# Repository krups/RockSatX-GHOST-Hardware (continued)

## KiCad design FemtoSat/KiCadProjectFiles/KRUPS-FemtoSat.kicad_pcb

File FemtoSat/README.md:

# KRUPS-FemtoSat
PCB design files and documentation for the femto-satellites used in the University of Kentucky's 2025 RockSat-XG KRUPS payload

### PCB Render

### Components
- [Raspberry Pi Pico 2 W (4MB Flash)](https://datasheets.raspberrypi.com/picow/pico-2-w-datasheet.pdf)
- [Fanstel LR62XE 1W 868/915MHz LoRa Modem](https://static1.squarespace.com/static/561459a2e4b0b39f5cefa12e/t/63ddc4b1dd728b424f1a6c23/1675478197953/LR62E_LR62XE_M262X840XE_Product+Specifications.pdf)
- [BME280 Temperature, Pressure, Humidity Sensor](https://www.bosch-sensortec.com/media/boschsensortec/downloads/datasheets/bst-bme280-ds002.pdf)
- [BNO086 9-Axis IMU](https://www.mouser.com/datasheet/2/1480/BNO080_085_Datasheet-3196201.pdf)

### Pin Mapping
| Pico 2 W GPIO Pin | Net Name |
| --- | --- |
| GPIO6 | BNO086_HINTN |
| GPIO7 | BNO086_RESET (active low)|
| GPIO8 | I2C_SDA |
| GPIO9 | I2C_SCL |
| GPIO16 | SPI_MISO |
| GPIO17 | SPI_NSS |
| GPIO18 | SPI_CLK |
| GPIO19 | SPI_MOSI |
| GPIO20 | LORA_ANTSW |
| GPIO21 | LORA_RESET (active low)|
| GPIO22 | LORA_BUSY |
| GPIO26 | LORA_DIO1 |

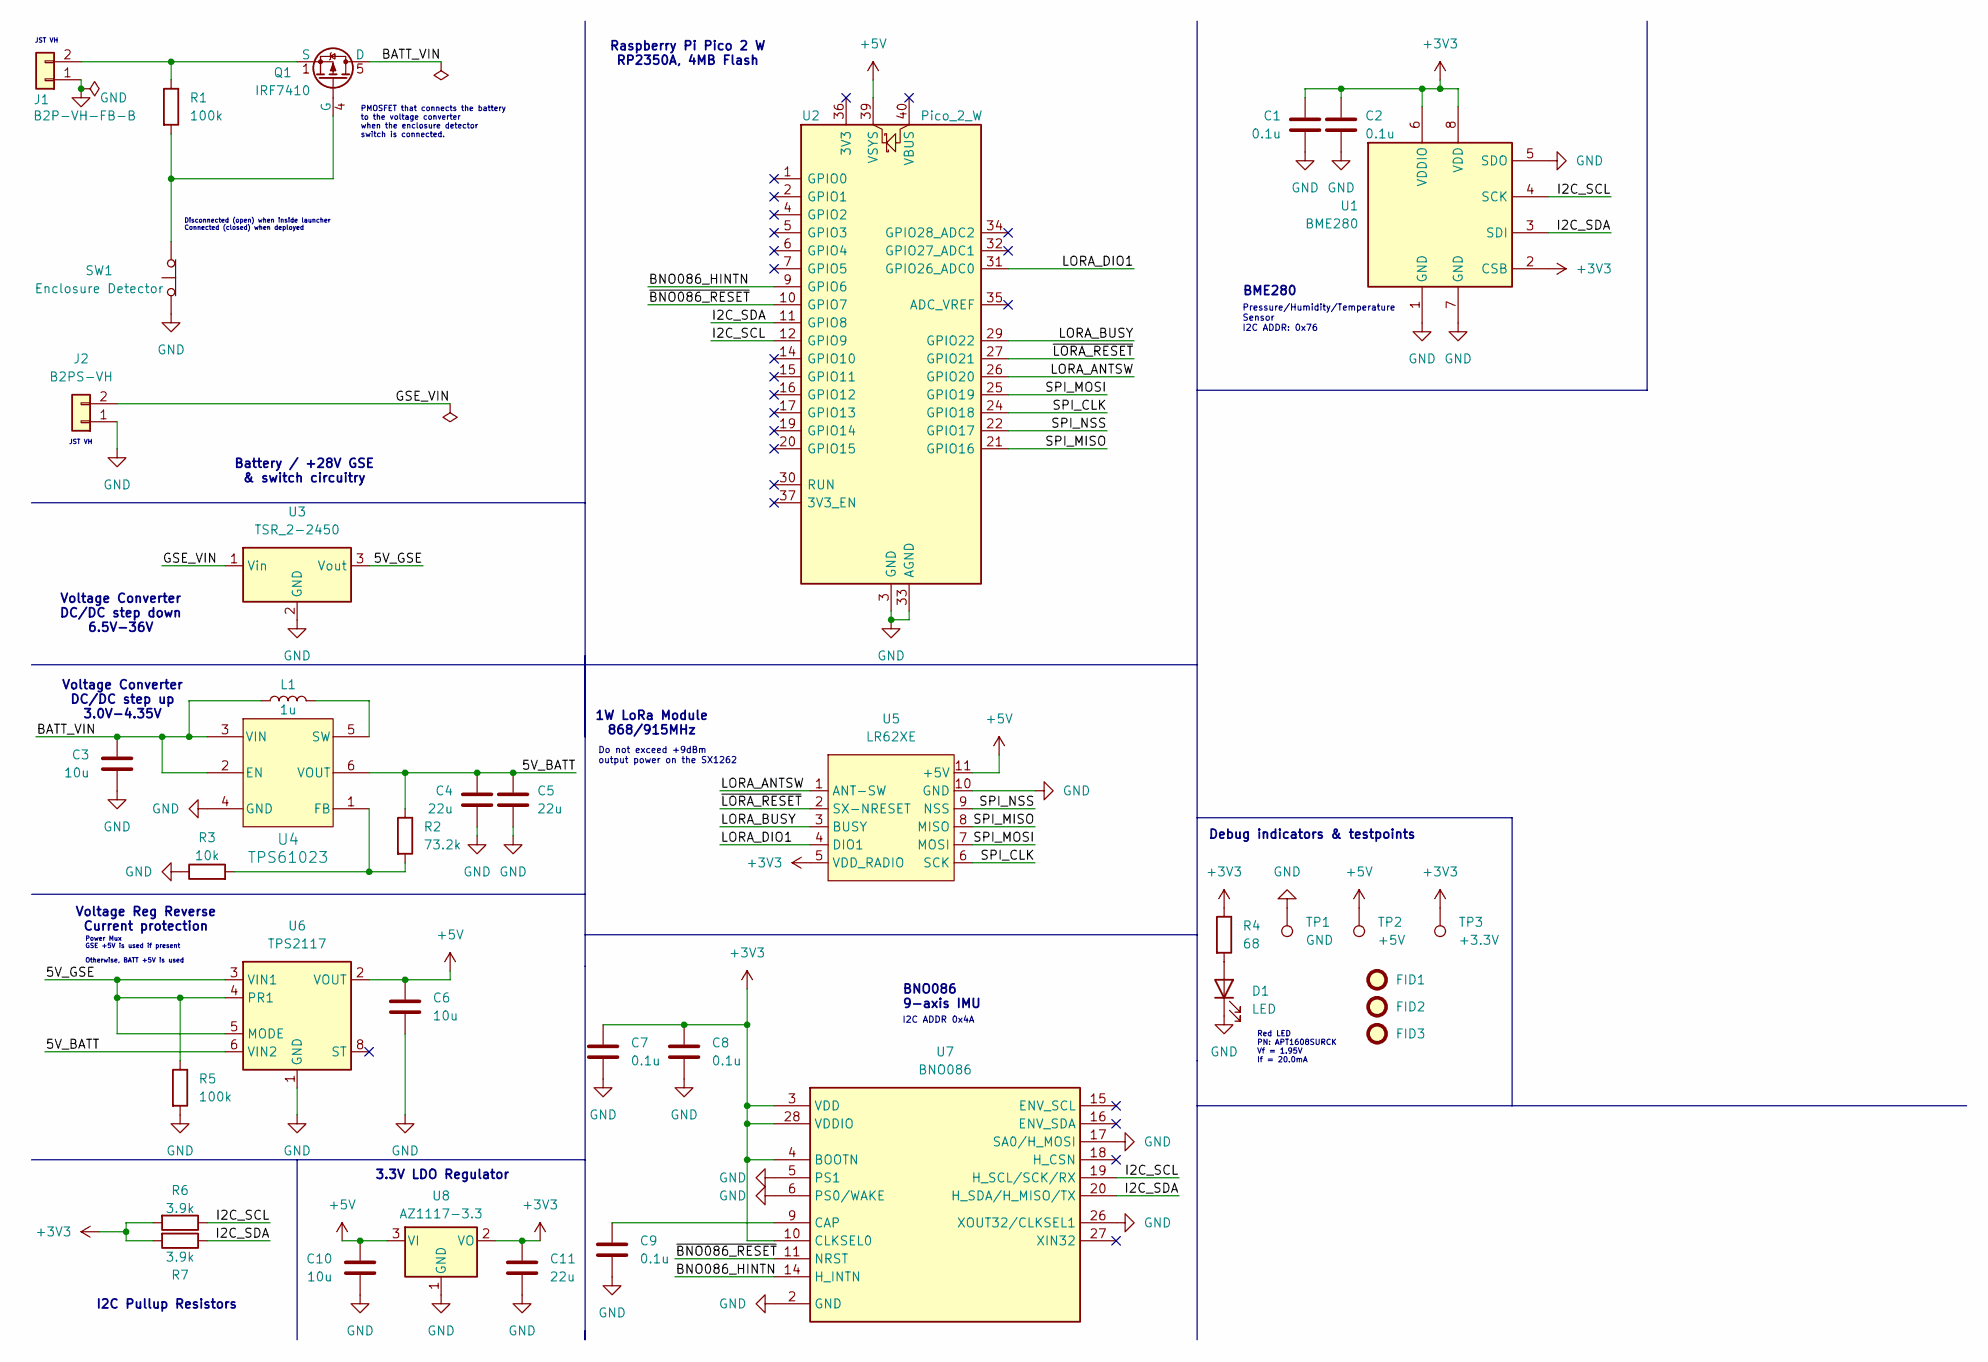
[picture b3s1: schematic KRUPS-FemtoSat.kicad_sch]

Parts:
C1, C2, C7, C8, C9: 0.1u; C_0603_1608Metric_Pad1.08x0.95mm_HandSolder; Digikey Part Number CC0603KRX7R7BB104
C3, C6, C10: 10u; C_0805_2012Metric_Pad1.18x1.45mm_HandSolder; Digikey Part Number CL21A106KOQNNNG
C4, C5, C11: 22u; C_0805_2012Metric_Pad1.18x1.45mm_HandSolder; Digikey Part Number CL21A226MPQNNNE
D1: LED; D_0603_1608Metric_Pad1.05x0.95mm_HandSolder; Digikey Part Number APT1608SURCK
FID1, FID2, FID3: Fiducial; Fiducial_0.5mm_Mask1mm
J1: B2P-VH-FB-B; JST_VH_B2P-VH-FB-B_1x02_P3.96mm_Vertical; Digikey Part Number B2P-VH-FB-B
J2: B2PS-VH; JST_VH_S2P-VH_1x02_P3.96mm_Horizontal; Digikey Part Number B2PS-VH
L1: 1u; L_Coilcraft_XxL4030; Digikey Part Number XEL4030-102MEC
Q1: IRF7410; SOIC-8_3.9x4.9mm_P1.27mm; Digikey Part Number IRF7410TRPBF
R1, R5: 100k; R_0603_1608Metric_Pad0.98x0.95mm_HandSolder; Digikey Part Number RMCF0603FT100K
R2: 73.2k; R_0603_1608Metric_Pad0.98x0.95mm_HandSolder; Digikey Part Number RC0603FR-0773K2L
R3: 10k; R_0603_1608Metric_Pad0.98x0.95mm_HandSolder; Digikey Part Number RC0603FR-0710KL
R4: 68; R_0603_1608Metric_Pad0.98x0.95mm_HandSolder; Digikey Part Number RC0603JR-0768RL
R6, R7: 3.9k; R_0603_1608Metric_Pad0.98x0.95mm_HandSolder; Digikey Part Number ERJ-3EKF3901V
SW1: Enclosure Detector; LC1258OANP; Digikey Part Number LC1258OANP
TP1: GND; TestPoint_Pad_2.0x2.0mm
TP2: +5V; TestPoint_Pad_2.0x2.0mm
TP3: +3.3V; TestPoint_Pad_2.0x2.0mm
U1: BME280; Bosch_LGA-8_2.5x2.5mm_P0.65mm_ClockwisePinNumbering; Digikey Part Number BME280
U2: Pico_2_W; RaspberryPi_Pico2_W_SMD; Digikey Part Number 2648-SC1633CT-ND
U3: TSR_2-2450; CONV_TSR_2-2450; Digikey Part Number TSR 2-2450
U4: TPS61023; SOT-563; Digikey Part Number TPS61023DRLR
U5: LR62XE; Digikey Part Number LR62XE
U6: TPS2117; SOT-583-8; Digikey Part Number TPS2117DRLR
U7: BNO086; LGA-28_5.2x3.8mm_P0.5mm; Manufacturer_Part_Number BNO086; Mouser Part Number 526-BNO086
U8: AZ1117-3.3; SOT-89-3_Handsoldering; Digikey Part Number AZ1117CR2-3.3TRG1

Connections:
+3V3: C1.1, C2.1, C7.1, C8.1, C11.1, R4.1, R6.2, R7.2, TP3.1, U1.2 (CSB), U1.6 (VDDIO), U1.8 (VDD), U5.5 (VDD_RADIO), U7.3 (VDD), U7.4 (BOOTN), U7.10 (CLKSEL0), U7.28 (VDDIO), U8.2 (VO)
+5V: C6.1, C10.1, TP2.1, U2.39 (VSYS), U5.11 (+5V), U6.2 (VOUT), U6.7 (VOUT), U8.3 (VI)
/5V_BATT: C4.1, C5.1, R2.1, U4.6 (VOUT), U6.6 (VIN2)
/5V_GSE: R5.1, U3.3 (Vout), U6.3 (VIN1), U6.4 (PR1), U6.5 (MODE)
/BATT_VIN: C3.1, L1.1, Q1.5 (D), Q1.6, Q1.7, Q1.8, U4.2 (EN), U4.3 (VIN)
/BNO086_HINTN: U2.9 (GPIO6), U7.14 (H_INTN)
/GSE_VIN: J2.2, U3.1 (Vin)
/I2C_SCL: R6.1, U1.4 (SCK), U2.12 (GPIO9), U7.19 (H_SCL/SCK/RX)
/I2C_SDA: R7.1, U1.3 (SDI), U2.11 (GPIO8), U7.20 (H_SDA/H_MISO/TX)
/LORA_ANTSW: U2.26 (GPIO20), U5.1 (ANT-SW)
/LORA_BUSY: U2.29 (GPIO22), U5.3 (BUSY)
/LORA_DIO1: U2.31 (GPIO26_ADC0), U5.4 (DIO1)
/SPI_CLK: U2.24 (GPIO18), U5.6 (SCK)
/SPI_MISO: U2.21 (GPIO16), U5.8 (MISO)
/SPI_MOSI: U2.25 (GPIO19), U5.7 (MOSI)
/SPI_NSS: U2.22 (GPIO17), U5.9 (NSS)
/~BNO086_RESET: U2.10 (GPIO7), U7.11 (NRST)
/~LORA_RESET: U2.27 (GPIO21), U5.2 (SX-NRESET)
GND: C1.2, C2.2, C3.2, C4.2, C5.2, C6.2, C7.2, C8.2, C9.2, C10.2, C11.2, D1.1 (K), J1.1, J2.1, R3.1, R5.2, SW1.1 (A), TP1.1, U1.1 (GND), U1.5 (SDO), U1.7 (GND), U2.3 (GND), U2.8 (GND), U2.13 (GND), U2.18 (GND), U2.23 (GND), U2.28 (GND), U2.33 (AGND), U2.38 (GND), U3.2 (GND), U4.4 (GND), U5.10 (GND), U5.12 (GND), U6.1 (GND), U7.2 (GND), U7.5 (PS1), U7.6 (PS0/WAKE), U7.17 (SA0/H_MOSI), U7.25 (GND), U7.26 (XOUT32/CLKSEL1), U8.1 (GND)
unnamed: D1.2 (A), R4.2
unnamed: J1.2, Q1.1 (S), Q1.2, Q1.3, R1.1
unnamed: Q1.4 (G), R1.2, SW1.2 (B)
unnamed: R2.2, R3.2, U4.1 (FB)
unnamed: L1.2, U4.5 (SW)
unnamed: C9.1, U7.9 (CAP)

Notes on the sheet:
Power Mux GSE +5V is used if present Otherwise, BATT +5V is used
I2C ADDR 0x4A
JST VH
Red LED PN: APT1608SURCK Vf = 1.95V If = 20.0mA
Pressure/Humidity/Temperature Sensor I2C ADDR: 0x76
3.3V LDO Regulator
I2C Pullup Resistors
Voltage Converter DC/DC step down 6.5V-36V
Disconnected (open) when inside launcher Connected (closed) when deployed
Battery / +28V GSE & switch circuitry
PMOSFET that connects the battery to the voltage converter when the enclosure detector switch is connected.
Voltage Reg Reverse Current protection
BNO086 9-axis IMU
BME280
Do not exceed +9dBm output power on the SX1262
Raspberry Pi Pico 2 W RP2350A, 4MB Flash
Debug indicators & testpoints
1W LoRa Module 868/915MHz
Voltage Converter DC/DC step up 3.0V-4.35V

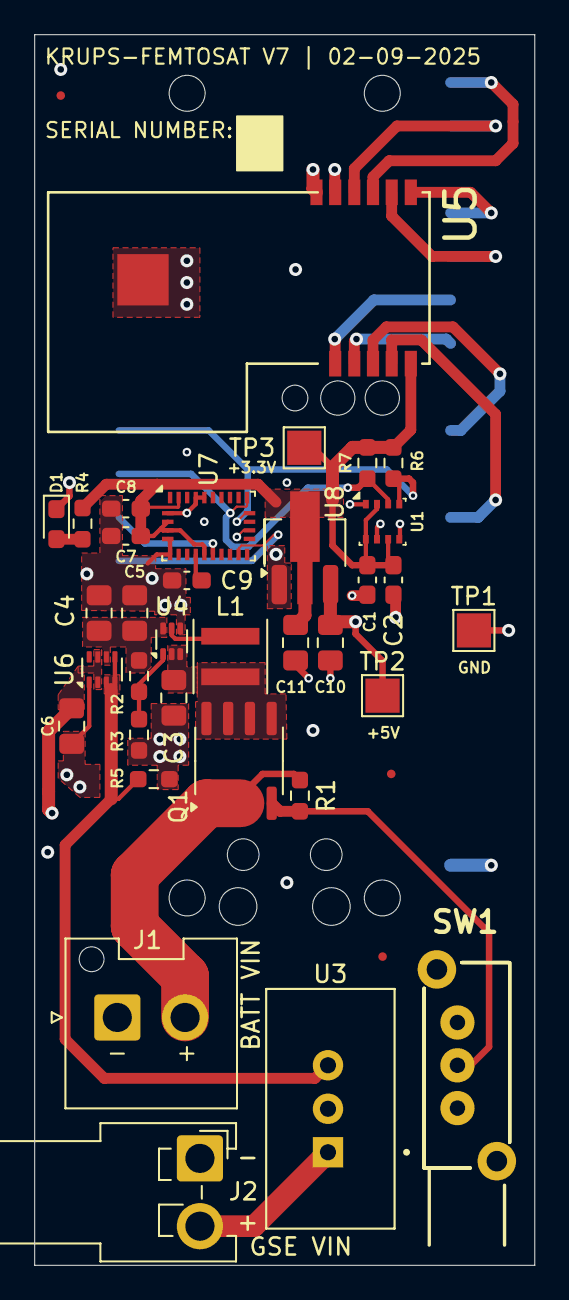
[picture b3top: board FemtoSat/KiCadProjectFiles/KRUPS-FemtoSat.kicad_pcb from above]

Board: 4 copper layers, 29.2 x 71.9 mm, 38 parts (1 on the bottom side), 25 nets.

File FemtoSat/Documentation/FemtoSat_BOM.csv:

"Reference","Value","Description","Qty","Digikey Part Number","DNP"
"C1,C2,C7,C8,C9","0.1u","0.1uF, 16V, X7R, SMD 0603","5","CC0603KRX7R7BB104",""
"C3,C6,C10","10u","10uF, 16V, X5R, SMD 0805","3","CL21A106KOQNNNG",""
"C4,C5,C11","22u","22uF, 10V, X5R, SMD 0805","3","CL21A226MPQNNNE",""
"D1","LED","LED, 1.95V Vf, 20mA If, SMD 0603","1","APT1608SURCK",""
"J1","B2P-VH-FB-B","JST-VH 2 Pin Connector, Shielded, Vertical","1","B2P-VH-FB-B",""
"J2","B2PS-VH","JST-VH 2 Pin Connector, Horizontal","1","B2PS-VH",""
"L1","1u","1uH Inductor, Shielded","1","XEL4030-102MEC",""
"Q1","IRF7410","PMOSFET, SOIC-8","1","IRF7410TRPBF",""
"R1,R5","100k","100K OHM, 1%, 1/10W, SMD 0603","2","RMCF0603FT100K",""
"R2","73.2k","73.2K OHM, 1%, 1/10W, SMD 0603","1","RC0603FR-0773K2L",""
"R3","10k","10K OHM, 1%, 1/10W, SMD 0603","1","RC0603FR-0710KL",""
"R4","68","68 OHM, 5%, 1/10W, SMD 0603","1","RC0603JR-0768RL",""
"R6,R7","3.9k","3.9K OHM, 1%, 1/10W, SMD 0603","2","ERJ-3EKF3901V",""
"SW1","Enclosure Detector","SPDT Push Switch, Non-Latching","1","LC1258OANP",""
"U1","BME280","3-in-1 sensor, humidity, pressure, temperature, I2C and SPI interface, 1.71-3.6V, LGA-8","1","BME280",""
"U2","Pico_2_W","Versatile and inexpensive microcontroller module powered by an RP2350 dual-core processor","1","2648-SC1633CT-ND",""
"U3","TSR_2-2450","1A step-down regulator module, fixed 5V output voltage, 5-36V input voltage, -40°C to +85°C temperature range, TO-220 compatible LM78xx replacement","1","TSR 2-2450",""
"U4","TPS61023","TPS61023 Boost Converter","1","TPS61023DRLR",""
"U5","LR62XE","1W LoRa Module","1","LR62XE",""
"U6","TPS2117","2 Channnels Power Mux with Manual and Priority Switchover, 1.6-5.5V Input Voltage, 2.5A Output Current, Ron 40 mOhm, SOT-583-8","1","TPS2117DRLR",""
"U7","BNO086","Accelerometer, Gyroscope, Magnetometer, Temperature, 9 Axis Sensor IC, SPI Output","1","BNO086",""
"U8","AZ1117-3.3","1A 20V Fixed LDO Linear Regulator, 3.3V, SOT-89/SOT-223/TO-220/TO-252/TO-263","1","AZ1117CR2-3.3TRG1",""

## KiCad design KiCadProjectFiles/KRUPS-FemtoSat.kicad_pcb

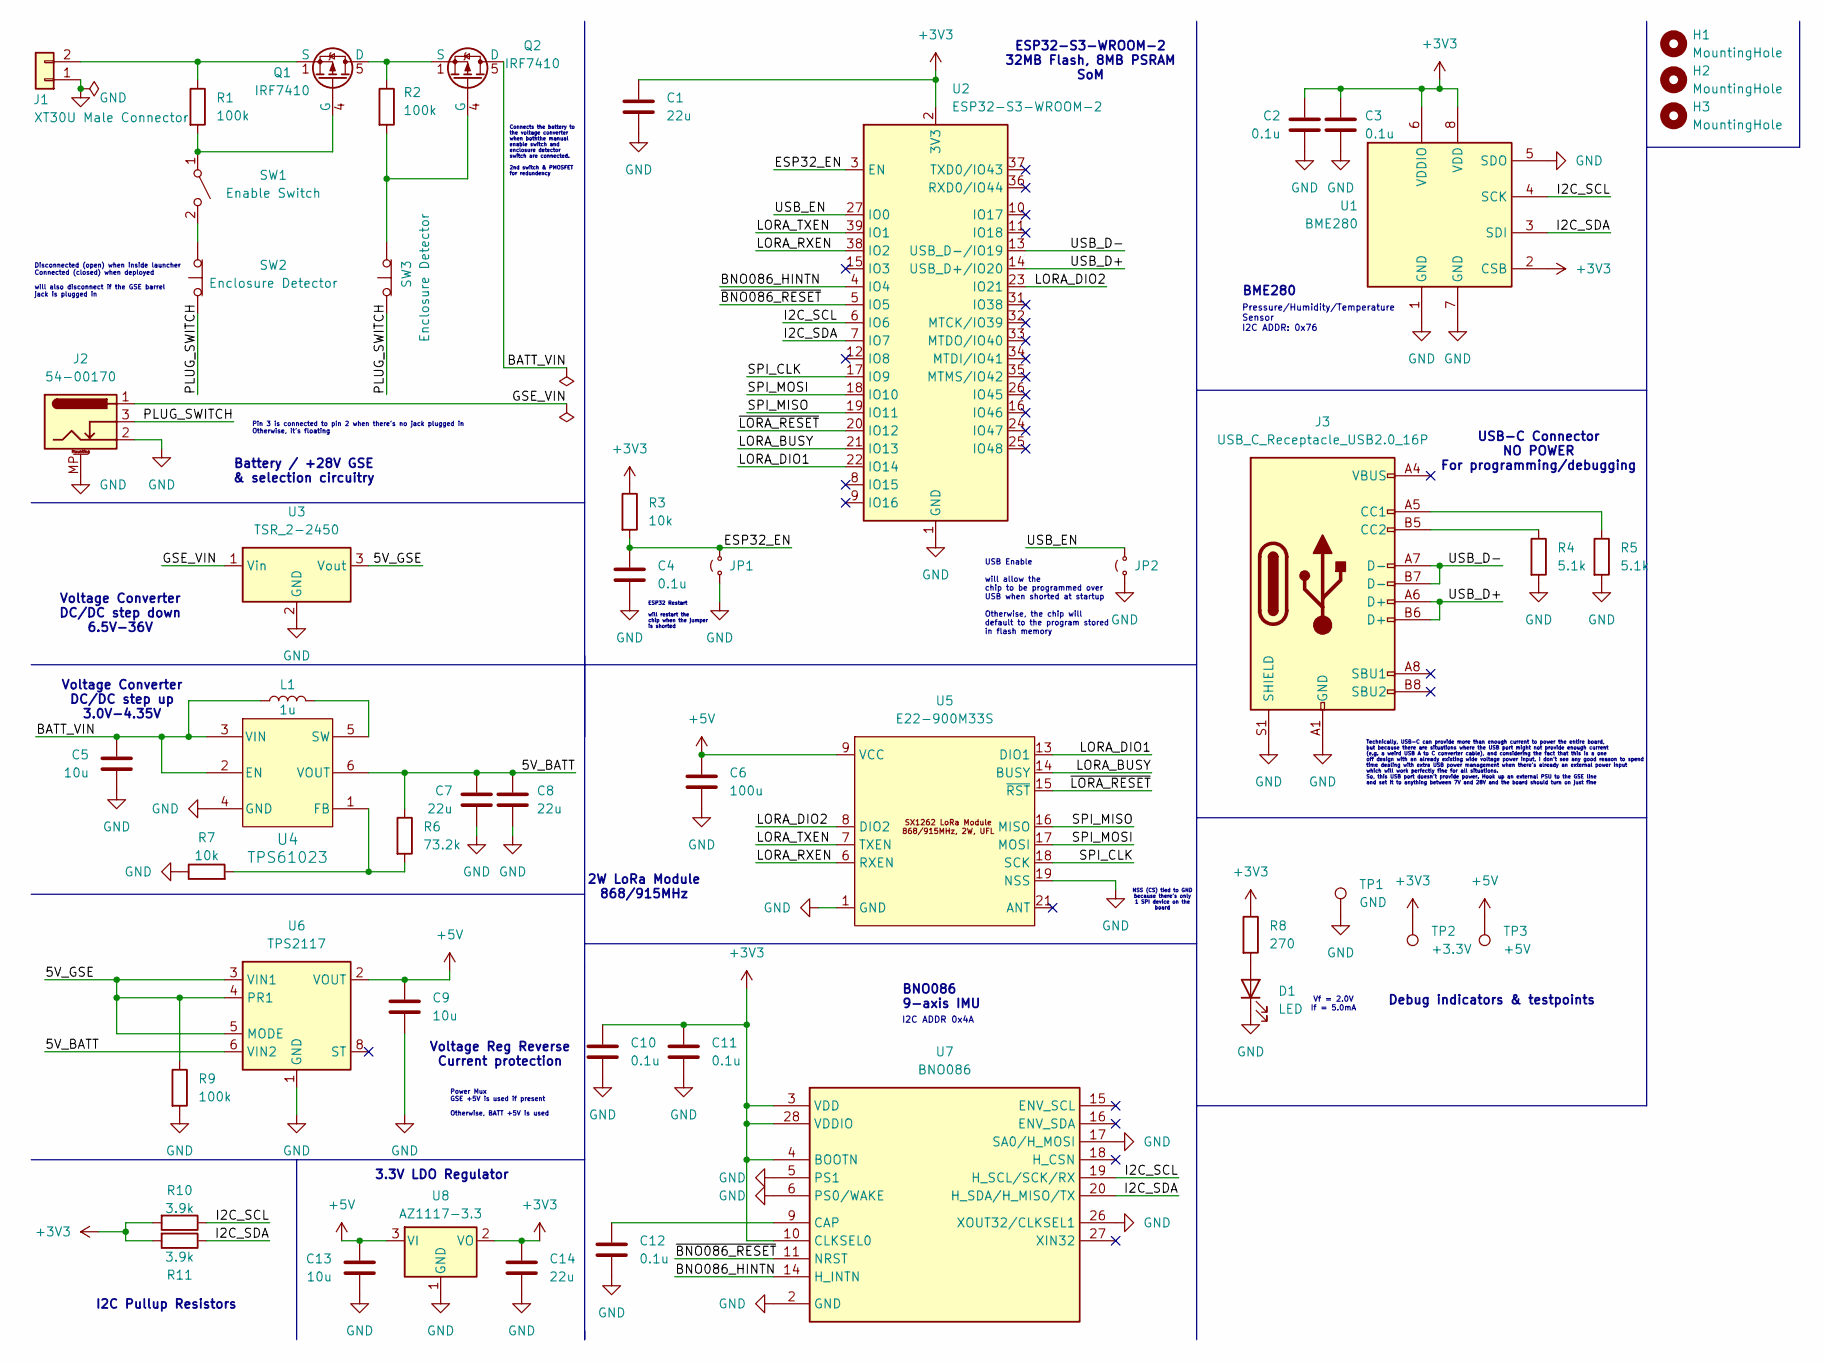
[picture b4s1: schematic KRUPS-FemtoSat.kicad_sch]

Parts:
C1, C7, C8, C14: 22u; C_0805_2012Metric_Pad1.18x1.45mm_HandSolder
C2, C3, C4, C10, C11, C12: 0.1u; C_0603_1608Metric_Pad1.08x0.95mm_HandSolder
C5, C9, C13: 10u; C_0805_2012Metric_Pad1.18x1.45mm_HandSolder
C6: 100u; C_1206_3216Metric_Pad1.33x1.80mm_HandSolder
D1: LED; D_0603_1608Metric_Pad1.05x0.95mm_HandSolder
H1, H2: MountingHole; MountingHole_2.2mm_M2
H3: MountingHole; MountingHole_2.2mm_M2_DIN965_Pad
J1: XT30U Male Connector; AMASS_XT30U-M_1x02_P5.0mm_Vertical
J2: 54-00170; TENSILITY_54-00170
J3: USB_C_Receptacle_USB2.0_16P; USB_C_Receptacle_GCT_USB4110
JP1, JP2: Jumper_2_Small_Open; TestPoint_2Pads_Pitch2.54mm_Drill0.8mm
L1: 1u; L_Coilcraft_XxL4030
Q1, Q2: IRF7410; SOIC-8_3.9x4.9mm_P1.27mm
R1, R2, R9: 100k; R_0603_1608Metric_Pad0.98x0.95mm_HandSolder
R3, R7: 10k; R_0603_1608Metric_Pad0.98x0.95mm_HandSolder
R4, R5: 5.1k; R_0603_1608Metric_Pad0.98x0.95mm_HandSolder
R6: 73.2k; R_0603_1608Metric_Pad0.98x0.95mm_HandSolder
R8: 270; R_0603_1608Metric_Pad0.98x0.95mm_HandSolder
R10, R11: 3.9k; R_0603_1608Metric_Pad0.98x0.95mm_HandSolder
SW1: Enable Switch; SW_DIP_SPSTx01_Slide_6.7x4.1mm_W7.62mm_P2.54mm_LowProfile
SW2, SW3: Enclosure Detector; LC1258OANP
TP1: GND; TestPoint_Pad_1.5x1.5mm
TP2: +3.3V; TestPoint_Pad_1.0x1.0mm
TP3: +5V; TestPoint_Pad_1.5x1.5mm
U1: BME280; Bosch_LGA-8_2.5x2.5mm_P0.65mm_ClockwisePinNumbering
U2: ESP32-S3-WROOM-2
U3: TSR_2-2450; Converter_DCDC_TRACO_TSR-1_THT
U4: TPS61023; SOT-563
U5: E22-900M33S; E22-XXXM33S
U6: TPS2117; SOT-583-8
U7: BNO086; LGA-28_5.2x3.8mm_P0.5mm; Manufacturer_Part_Number BNO086; Mouser Part Number 526-BNO086
U8: AZ1117-3.3; SOT-89-3_Handsoldering

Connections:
+3V3: C1.1, C2.1, C3.1, C10.1, C11.1, C14.1, R3.1, R8.1, R10.2, R11.2, TP2.1, U1.2 (CSB), U1.6 (VDDIO), U1.8 (VDD), U2.2 (3V3), U7.3 (VDD), U7.4 (BOOTN), U7.10 (CLKSEL0), U7.28 (VDDIO), U8.2 (VO)
+5V: C6.1, C9.1, C13.1, TP3.1, U5.9 (VCC), U5.10 (VCC), U6.2 (VOUT), U6.7 (VOUT), U8.3 (VI)
/5V_BATT: C7.1, C8.1, R6.1, U4.6 (VOUT), U6.6 (VIN2)
/5V_GSE: R9.1, U3.3 (Vout), U6.3 (VIN1), U6.4 (PR1), U6.5 (MODE)
/BATT_VIN: C5.1, L1.1, Q2.5 (D), Q2.6, Q2.7, Q2.8, U4.2 (EN), U4.3 (VIN)
/BNO086_HINTN: U2.4 (IO4), U7.14 (H_INTN)
/ESP32_EN: C4.1, JP1.2 (B), R3.2, U2.3 (EN)
/GSE_VIN: J2.1, U3.1 (Vin)
/I2C_SCL: R10.1, U1.4 (SCK), U2.6 (IO6), U7.19 (H_SCL/SCK/RX)
/I2C_SDA: R11.1, U1.3 (SDI), U2.7 (IO7), U7.20 (H_SDA/H_MISO/TX)
/LORA_BUSY: U2.21 (IO13), U5.14 (BUSY)
/LORA_DIO1: U2.22 (IO14), U5.13 (DIO1)
/LORA_DIO2: U2.23 (IO21), U5.8 (DIO2)
/LORA_RXEN: U2.38 (IO2), U5.6 (RXEN)
/LORA_TXEN: U2.39 (IO1), U5.7 (TXEN)
/PLUG_SWITCH: J2.3, SW2.1 (A), SW3.1 (A)
/SPI_CLK: U2.17 (IO9), U5.18 (SCK)
/SPI_MISO: U2.19 (IO11), U5.16 (MISO)
/SPI_MOSI: U2.18 (IO10), U5.17 (MOSI)
/USB_D+: J3.A6 (D+), J3.B6 (D+), U2.14 (USB_D+/IO20)
/USB_D-: J3.A7 (D-), J3.B7 (D-), U2.13 (USB_D-/IO19)
/USB_EN: JP2.2 (B), U2.27 (IO0)
/~BNO086_RESET: U2.5 (IO5), U7.11 (NRST)
/~LORA_RESET: U2.20 (IO12), U5.15 (~RST)
GND: C1.2, C2.2, C3.2, C4.2, C5.2, C6.2, C7.2, C8.2, C9.2, C10.2, C11.2, C12.2, C13.2, C14.2, D1.1 (K), J1.1, J2.2, J2.MP (MountPin), J3.A1 (GND), J3.A12 (GND), J3.B1 (GND), J3.B12 (GND), J3.S1 (SHIELD), JP1.1 (A), JP2.1 (A), R4.2, R5.2, R7.1, R9.2, TP1.1, U1.1 (GND), U1.5 (SDO), U1.7 (GND), U2.1 (GND), U2.40 (GND), U2.41 (GND), U3.2 (GND), U4.4 (GND), U5.1 (GND), U5.2 (GND), U5.3 (GND), U5.4 (GND), U5.5 (GND), U5.11 (GND), U5.12 (GND), U5.19 (NSS), U5.20 (GND), U5.22 (GND), U6.1 (GND), U7.2 (GND), U7.5 (PS1), U7.6 (PS0/WAKE), U7.17 (SA0/H_MOSI), U7.25 (GND), U7.26 (XOUT32/CLKSEL1), U8.1 (GND)
unnamed: D1.2 (A), R8.2
unnamed: J1.2, Q1.1 (S), Q1.2, Q1.3, R1.1
unnamed: J3.A5 (CC1), R5.1
unnamed: J3.B5 (CC2), R4.1
unnamed: Q1.5 (D), Q1.6, Q1.7, Q1.8, Q2.1 (S), Q2.2, Q2.3, R2.1
unnamed: Q1.4 (G), R1.2, SW1.1 (A)
unnamed: Q2.4 (G), R2.2, SW3.2 (B)
unnamed: SW1.2 (B), SW2.2 (B)
unnamed: R6.2, R7.2, U4.1 (FB)
unnamed: L1.2, U4.5 (SW)
unnamed: C12.1, U7.9 (CAP)

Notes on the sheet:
Power Mux GSE +5V is used if present Otherwise, BATT +5V is used
I2C ADDR 0x4A
Vf = 2.0V If = 5.0mA
Pressure/Humidity/Temperature Sensor I2C ADDR: 0x76
3.3V LDO Regulator
I2C Pullup Resistors
Voltage Converter DC/DC step down 6.5V-36V
Disconnected (open) when inside launcher Connected (closed) when deployed will also disconnect if the GSE barrel jack is plugged in
Battery / +28V GSE & selection circuitry
Connects the battery to the voltage converter when boththe manual enable switch and enclosure detector switch are connected. 2nd switch & PMOSFET for redundency
Voltage Reg Reverse Current protection
ESP32 Restart will restart the chip when the jumper is shorted
BNO086 9-axis IMU
USB-C Connector NO POWER For programming/debugging
BME280
NSS (CS) tied to GND because there's only 1 SPI device on the board
ESP32-S3-WROOM-2 32MB Flash, 8MB PSRAM SoM
Debug indicators & testpoints
2W LoRa Module 868/915MHz
Pin 3 is connected to pin 2 when there's no jack plugged in Otherwise, it's floating
Voltage Converter DC/DC step up 3.0V-4.35V
USB Enable will allow the chip to be programmed over USB when shorted at startup Otherwise, the chip will default to the program stored in flash memory
Technically, USB-C can provide more than enough current to power the entire board, but because there are situations where the USB port might not provide enough current (e.g. a weird USB A to C converter cable), and considering the fact that this is a one off design with an already existing wide vol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

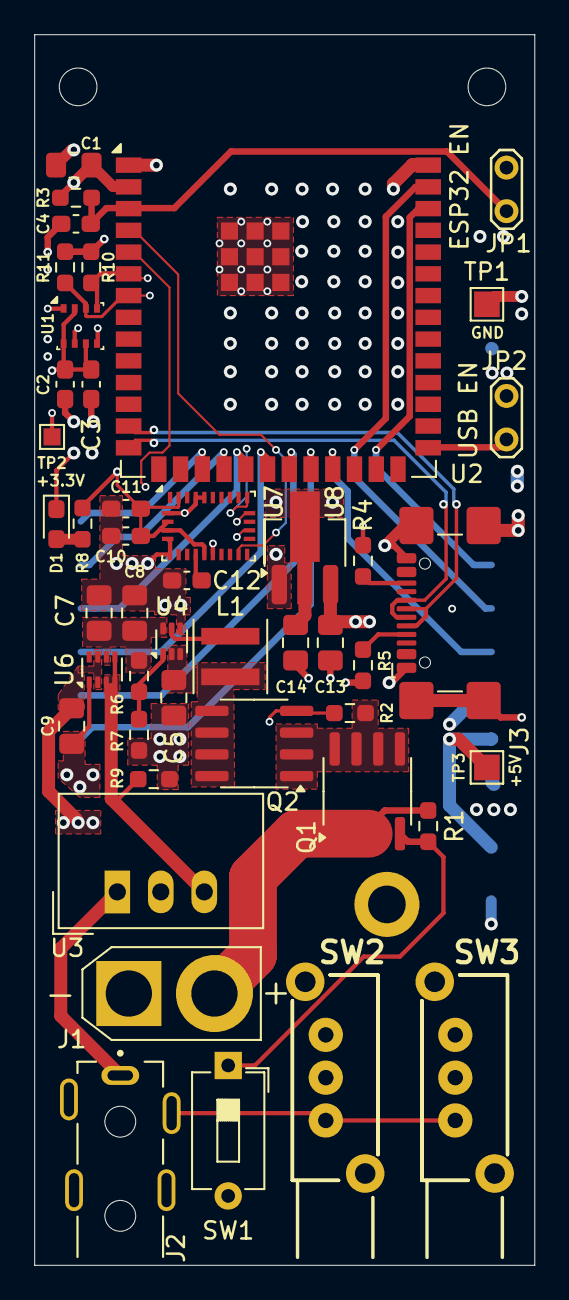
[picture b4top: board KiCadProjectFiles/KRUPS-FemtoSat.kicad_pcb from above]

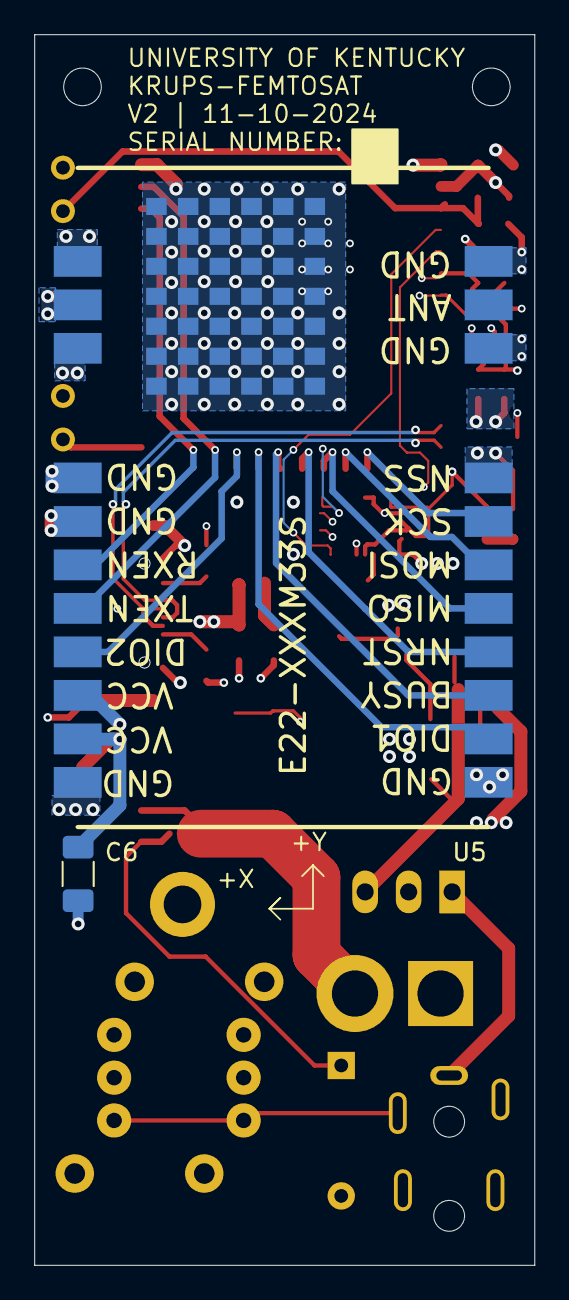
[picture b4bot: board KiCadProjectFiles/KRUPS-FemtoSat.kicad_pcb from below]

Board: 4 copper layers, 29.2 x 71.9 mm, 51 parts (2 on the bottom side), 36 nets.

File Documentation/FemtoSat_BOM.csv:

PCB Version,V1.1,,,,
BOM Last Updated Date,10/31/24,,,,
,,,,,
Reference,Description,Manufacturer / Part Number,Qty,Ordering Link,
"C1,C7,C8,C14","22uF, 10V, X5R, SMD 0805",CL21A226MPQNNNE,4,https://www.digikey.com/en/products/detail/samsung-electro-m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,
"C2,C3,C4,C10,C11,C12","0.1uF, 16V, X7R, SMD 0603",CC0603KRX7R7BB104,6,https://www.digikey.com/en/products/detail/yageo/CC0603KRX7R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,
"C5,C9,C13","10uF, 16V, X5R, SMD 0805",CL21A106KOQNNNG,3,https://www.digikey.com/en/products/detail/samsung-electro-m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,
C6,"100uF, 6.3V, X5R. SMD 1206",CL31A107MQHNNWE,1,https://www.digikey.com/en/products/detail/samsung-electro-m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,
D1,"LED, 2V Vf, 5mA If, SMD 0603",B1931UD05D000314U1930,1,https://www.digikey.com/en/products/detail/harvatek-corporat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,
J1,XT30U Male Connector,AMASS \ XT30U-M,1,https://www.digikey.com/en/products/detail/dfrobot/FIT0586/9559255,
J2,"Barrel Connector Jack, 0.7mm X 2.35mm, Rated 48V",Tensility \ 54-00170,1,https://www.digikey.com/en/products/detail/tensility-interna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,
J3,"USB 2.0 Type-C Jack, 16+8 Pin",GCT \ USB4110-GF-A,1,https://www.digikey.com/en/products/detail/gct/USB4110-GF-A/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,
L1,"1uH Inductor, Shielded",Coilcraft \ XEL4030-102MEC,1,https://www.digikey.com/en/products/detail/coilcraft/XEL4030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,
"Q1,Q2",IRF7410 PMOSFET,Infineon Technologies \ IRF7410TRPBF,2,https://www.digikey.com/en/products/detail/infineon-technolo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,
"R1,R2,R9","100K OHM, 1%, 1/10W, SMD 0603",RMCF0603FT100K,3,https://www.digikey.com/en/products/detail/stackpole-electro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,
"R3,R7","10K OHM, 1%, 1/10W, SMD 0603",RC0603FR-0710KL,2,https://www.digikey.com/en/products/detail/yageo/RC0603FR-07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,
"R4,R5","5.1K OHM, 1%, 1/10W, SMD 0603",RC0603FR-075K1L,2,https://www.digikey.com/en/products/detail/yageo/RC0603FR-07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,
R6,"73.2K OHM, 1%, 1/10W, SMD 0603",RC0603FR-0773K2L,1,https://www.digikey.com/en/products/detail/yageo/RC0603FR-07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,
R8,"270 OHM, 5%, 1/10W, SMD 0603",RMCF0603JT270R,1,https://www.digikey.com/en/products/detail/stackpole-electro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,
"R10,R11","3.9K OHM, 1%, 1/10W, SMD 0603",ERJ-3EKF3901V,2,https://www.digikey.com/en/products/detail/panasonic-electro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,
SW1,DIP Switch,Same Sky \ DS04-254-1L-01BK,1,https://www.digikey.com/en/products/detail/same-sky-formerly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,
"SW2,SW3","SPDT Push Switch, Non-Latching",E-Switch \ LC1258OANP,2,https://www.digikey.com/en/products/detail/e-switch/LC1258OA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,
U1,BME280 Environmental Sensor,Bosch Sensortec \ BME280,1,https://www.digikey.com/en/products/detail/bosch-sensortec/B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,
U2,"ESP32-S3-WROOM-2, 32MB Flash, 8MB PSRAM",Espressif \ ESP32-S3-WROOM-2-N32R8V,1,https://www.digikey.com/en/products/detail/espressif-systems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,
U3,6.5V  28V DC DC Converter,Traco Power \ TSR 2-2450,1,https://www.digikey.com/en/products/detail/traco-power/TSR-2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,
U4,TPS61023 Boost Converter,Texas Instruments \ TPS61023DRLR,1,https://www.digikey.com/en/products/detail/texas-instruments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,
U5,E22-900M33S 2W LoRa Module,EBYTE \ E22-900M33S,1,https://www.lcsc.com/product-detail/LoRa-Modules_Chengdu-Eby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,An alternative option is https://www.aliexpress.us/item/3256806595412116.html
U6,TPS2117 Power Switch,Texas Instruments \ TPS2117DRLR,1,https://www.digikey.com/en/products/detail/texas-instruments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,
U7,BNO086 9-Axis IMU,CEVA Technologies \ BNO086,1,https://www.digikey.com/en/products/detail/ceva-technologies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,
U8,"AZ1117-3.3 LDO Regulator, SOT-89-3",Diodes Incorporated \ AZ1117CR2-3.3TRG1,1,https://www.digikey.com/en/products/detail/diodes-incorporat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,

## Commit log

2024-10-29 V1 Commit
    Initial V1 Design
2024-10-31 V1.1 Update
    - Replaced the ESP32-S3-WROOM-1U module with an ESP32-S3-WROOM-2 module (octal SPI flash, integrated PCB antenna)
    - Changed the pins assigned to LORA_TXEN/RXEN to avoid possible issues with 1.8V logic levels on IO47 & IO48
    - Updated relevant documentation
2024-10-31 changed version marker on back silkscreen to v1.1
2024-11-11 V2 Update. Added mounting holes, moved around some components, and added some silkscreen markers
2024-11-11 V3. Connected the SPI NSS of the LoRa modem to an IO pin rather than ground
2024-11-17 Reorganized repository, added initial files for the GHOST RocketStation
    - Changed the repository name from KRUPS-FemtoSat to RockSatX-GHOST-Hardware
    - Reorganized the repository, each individual PCB now gets its own folder
    - Added V1 files for the KRUPS-RocketStation
2024-11-17 Small fixes for RocketStation v1
    Modified RocketStation readme, fixed unconnected 3.3V test point, slightly changed async nets on schematic
2024-11-17 Fixed first line in readme
2024-11-21 Updated femtosat/rocketstation BOMs
2024-12-03 Added block diagrams for femtosat & rocketstation
2024-12-05 Added optional support for the LR62XE 1W radio
    - Created a breakout/adapter board for the LR62XE 1W LoRa radio
    - Modified the FemtoSat and RocketStation so that they'll be compatible with the adapter board
2024-12-05 added adapter pictures, changed adapter silkscreen
2024-12-28 Design Review Updates
    Large number of design changes to both the FemtoSat (V5) and RocketStation (V3)
    On both boards:
    - Swapped the ESP32-S3-WROOM-2 modules to WROOM-1 modules due to supply issues
    - Swapped power connectors to JST VH, data connectors to JST GH
    - Added "Space Systems Lab, University of Kentucky, Lexington KY, USA, Earth" to the silkscreens
    - Added test pads for IO pins, I2C bus, power
2024-12-28 Added fiducials to femtosat (v6) and rocketstation (v4)
2025-01-11 Corrected entries for C3 & C18 (100uF) on RocketStation BOM
2025-01-18 fixed title of rocketstation readme
2025-01-18 Updated block diagrams, added empty folder for capsule hardware
2025-01-22 Corrected part numbers for C3 and C18 in BOM
2025-02-11 Changed to Raspi Pico, 1W radio
    - Swapped the ESP32 S3 WROOM to a Raspberry Pi Pico 2 W on both the FemtoSat and RocketStation
    - Swapped to 1W LoRa module in place of the 2W EBYTE one
    - bunch of layout, documentation, miscellaneous changes
2025-02-21 Removed LR62XE adapter, corrected readme, fixed silkscreen on LR62XE footprint
2025-03-04 Uploaded files for main capsule PCB on the behalf of Cannon Shields
2025-03-13 Added femtosat verification program
2025-04-20 updated capsule schematic with improvised thermocouple changes. created schematic pdf
2025-06-24 Adding board render
